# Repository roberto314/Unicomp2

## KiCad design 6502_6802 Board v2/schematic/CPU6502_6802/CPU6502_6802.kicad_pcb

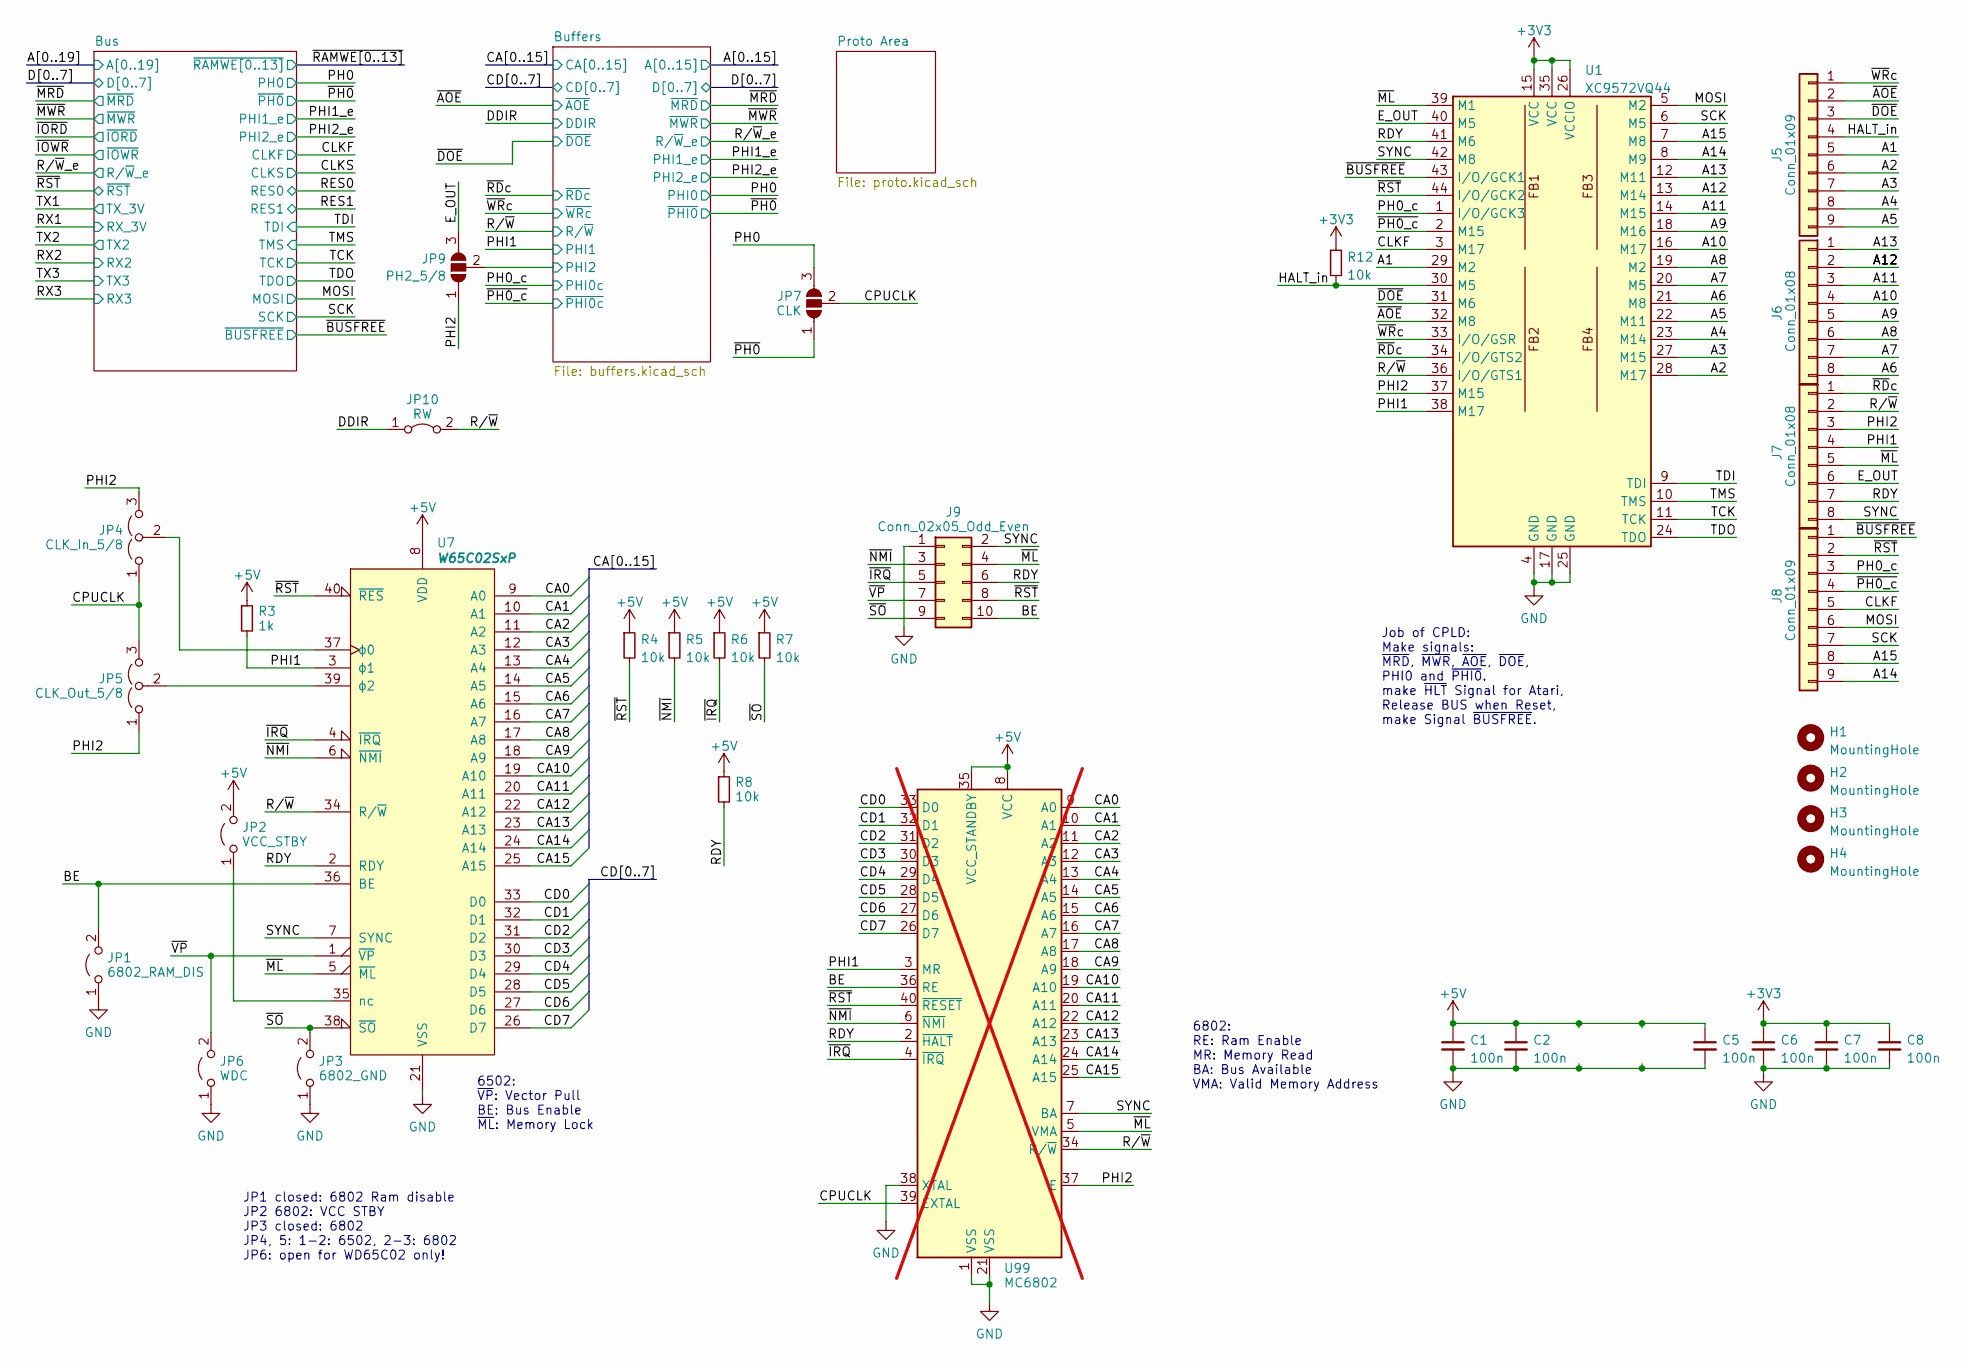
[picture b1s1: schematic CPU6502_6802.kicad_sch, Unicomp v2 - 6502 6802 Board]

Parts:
C1, C2, C5, C6, C7, C8: 100n; C_1206_3216Metric
H1, H2, H3, H4: MountingHole; MountingHole_3.2mm_M3
J5, J8: Conn_01x09; PinHeader_1x09_P2.54mm_Vertical
J6, J7: Conn_01x08; PinHeader_1x08_P2.54mm_Vertical
J9: Conn_02x05_Odd_Even; PinHeader_2x05_P2.54mm_Horizontal
JP1: 6802_RAM_DIS; SolderJumper-2_P1.3mm_Open_RoundedPad1.0x1.5mm
JP2: VCC_STBY; SolderJumper-2_P1.3mm_Open_RoundedPad1.0x1.5mm
JP3: 6802_GND; SolderJumper-2_P1.3mm_Open_RoundedPad1.0x1.5mm
JP4: CLK_In_5/8; SolderJumper-3_P1.3mm_Open_Pad1.0x1.5mm_NumberLabels
JP5: CLK_Out_5/8; SolderJumper-3_P1.3mm_Open_Pad1.0x1.5mm_NumberLabels
JP6: WDC; SolderJumper-2_P1.3mm_Open_RoundedPad1.0x1.5mm
JP7: CLK; SolderJumper-3_P1.3mm_Open_RoundedPad1.0x1.5mm_NumberLabels
JP9: PH2_5/8; SolderJumper-3_P1.3mm_Open_RoundedPad1.0x1.5mm_NumberLabels
JP10: RW; SolderJumper-2_P1.3mm_Bridged_RoundedPad1.0x1.5mm
R3: 1k; R_1206_3216Metric_Pad1.30x1.75mm_HandSolder
R4, R5, R6, R7, R8, R12: 10k; R_1206_3216Metric_Pad1.30x1.75mm_HandSolder
U1: XC9572VQ44; TQFP-44_10x10mm_P0.8mm
U7: W65C02SxP; DIP-40_W15.24mm_Socket_LongPads
U99: MC6802; DIP-40_W15.24mm; not fitted

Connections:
+3V3: C6.1, C7.1, C8.1, R12.1, U1.15 (VCC), U1.26 (VCCIO), U1.35 (VCC); also elsewhere on the board
+5V: C1.1, C2.1, C5.1, JP2.2 (B), R3.1, R4.1, R5.1, R6.1, R7.1, R8.1, U7.8 (VDD), U99.8 (VCC), U99.35 (VCC_STANDBY); also elsewhere on the board
/A1: J5.5, U1.29 (M2); also elsewhere on the board
/A2: J5.6, U1.28 (M17); also elsewhere on the board
/A3: J5.7, U1.27 (M15); also elsewhere on the board
/A4: J5.8, U1.23 (M14); also elsewhere on the board
/A5: J5.9, U1.22 (M11); also elsewhere on the board
/A6: J6.8, U1.21 (M8); also elsewhere on the board
/A7: J6.7, U1.20 (M5); also elsewhere on the board
/A8: J6.6, U1.19 (M2); also elsewhere on the board
/A9: J6.5, U1.18 (M16); also elsewhere on the board
/A10: J6.4, U1.16 (M17); also elsewhere on the board
/A11: J6.3, U1.14 (M15); also elsewhere on the board
/A12: J6.2, U1.13 (M14); also elsewhere on the board
/A13: J6.1, U1.12 (M11); also elsewhere on the board
/A14: J8.9, U1.8 (M9); also elsewhere on the board
/A15: J8.8, U1.7 (M8); also elsewhere on the board
/BE: J9.10, JP1.2 (B), U7.36 (BE), U99.36 (RE)
/Buffers/PHI2: JP9.2 (C); also elsewhere on the board
/CA0: U7.9 (A0), U99.9 (A0); also elsewhere on the board
/CA1: U7.10 (A1), U99.10 (A1); also elsewhere on the board
/CA2: U7.11 (A2), U99.11 (A2); also elsewhere on the board
/CA3: U7.12 (A3), U99.12 (A3); also elsewhere on the board
/CA4: U7.13 (A4), U99.13 (A4); also elsewhere on the board
/CA5: U7.14 (A5), U99.14 (A5); also elsewhere on the board
/CA6: U7.15 (A6), U99.15 (A6); also elsewhere on the board
/CA7: U7.16 (A7), U99.16 (A7); also elsewhere on the board
/CA8: U7.17 (A8), U99.17 (A8); also elsewhere on the board
/CA9: U7.18 (A9), U99.18 (A9); also elsewhere on the board
/CA10: U7.19 (A10), U99.19 (A10); also elsewhere on the board
/CA11: U7.20 (A11), U99.20 (A11); also elsewhere on the board
/CA12: U7.22 (A12), U99.22 (A12); also elsewhere on the board
/CA13: U7.23 (A13), U99.23 (A13); also elsewhere on the board
/CA14: U7.24 (A14), U99.24 (A14); also elsewhere on the board
/CA15: U7.25 (A15), U99.25 (A15); also elsewhere on the board
/CD0: U7.33 (D0), U99.33 (D0); also elsewhere on the board
/CD1: U7.32 (D1), U99.32 (D1); also elsewhere on the board
/CD2: U7.31 (D2), U99.31 (D2); also elsewhere on the board
/CD3: U7.30 (D3), U99.30 (D3); also elsewhere on the board
/CD4: U7.29 (D4), U99.29 (D4); also elsewhere on the board
/CD5: U7.28 (D5), U99.28 (D5); also elsewhere on the board
/CD6: U7.27 (D6), U99.27 (D6); also elsewhere on the board
/CD7: U7.26 (D7), U99.26 (D7); also elsewhere on the board
/CLKF: J8.5, U1.3 (M17); also elsewhere on the board
/CPUCLK: JP4.1 (A), JP5.3 (B), JP7.2 (C), U99.39 (EXTAL)
/DDIR: JP10.1 (A); also elsewhere on the board
/E_OUT: J7.6, JP9.3 (B), U1.40 (M5)
/HALT_in: J5.4, R12.2, U1.30 (M5)
/MOSI: J8.6, U1.5 (M2); also elsewhere on the board
/PH0: JP7.3 (B); also elsewhere on the board
/PH0_c: J8.3, U1.1 (I/O/GCK3); also elsewhere on the board
/PHI1: J7.4, R3.2, U1.38 (M17), U7.3 (ϕ1), U99.3 (MR); also elsewhere on the board
/PHI2: J7.3, JP4.3 (B), JP5.1 (A), JP9.1 (A), U1.37 (M15), U99.37 (E)
/RDY: J7.7, J9.6, R8.2, U1.41 (M6), U7.2 (RDY), U99.2 (~HALT)
/R/~W: J7.2, JP10.2 (B), U1.36 (I/O/GTS1), U7.34 (R/~W), U99.34 (R/~W); also elsewhere on the board
/SCK: J8.7, U1.6 (M5); also elsewhere on the board
/SYNC: J7.8, J9.2, U1.42 (M8), U7.7 (SYNC), U99.7 (BA)
/TCK: U1.11 (TCK); also elsewhere on the board
/TDI: U1.9 (TDI); also elsewhere on the board
/TDO: U1.24 (TDO); also elsewhere on the board
/TMS: U1.10 (TMS); also elsewhere on the board
/~AOE: J5.2, U1.32 (M8); also elsewhere on the board
/~BUSFREE: J8.1, U1.43 (I/O/GCK1); also elsewhere on the board
/~DOE: J5.3, U1.31 (M6); also elsewhere on the board
/~IRQ: J9.5, R6.2, U7.4 (~IRQ), U99.4 (~IRQ)
/~ML: J7.5, J9.4, U1.39 (M1), U7.5 (~ML), U99.5 (VMA)
/~NMI: J9.3, R5.2, U7.6 (~NMI), U99.6 (~NMI)
/~PH0_c: J8.4, U1.2 (M15); also elsewhere on the board
/~PH0: JP7.1 (A); also elsewhere on the board
/~RDc: J7.1, U1.34 (I/O/GTS2); also elsewhere on the board
/~RST: J8.2, J9.8, R4.2, U1.44 (I/O/GCK2), U7.40 (~RES), U99.40 (~RESET); also elsewhere on the board
/~SO: J9.9, JP3.2 (B), R7.2, U7.38 (~SO)
/~VP: J9.7, JP6.2 (B), U7.1 (~VP)
/~WRc: J5.1, U1.33 (I/O/GSR); also elsewhere on the board
GND: C1.2, C2.2, C5.2, C6.2, C7.2, C8.2, J9.1, JP1.1 (A), JP3.1 (A), JP6.1 (A), U1.4 (GND), U1.17 (GND), U1.25 (GND), U7.21 (VSS), U99.1 (VSS), U99.21 (VSS), U99.38 (XTAL); also elsewhere on the board
unnamed: JP2.1 (A), U7.35 (nc)
unnamed: JP4.2 (C), U7.37 (ϕ0)
unnamed: JP5.2 (C), U7.39 (ϕ2)

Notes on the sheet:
JP1 closed: 6802 Ram disable JP2 6802: VCC STBY JP3 closed: 6802 JP4, 5: 1-2: 6502, 2-3: 6802 JP6: open for WD65C02 only!
6802: RE: Ram Enable MR: Memory Read BA: Bus Available VMA: Valid Memory Address
Job of CPLD: Make signals: ~{MRD}, ~{MWR}, ~{AOE}, ~{DOE}, PHI0 and ~{PHI0}. make ~{HLT} Signal for Atari, Release BUS when Reset, make Signal ~{BUSFREE}.
6502: ~{VP}: Vector Pull BE: Bus Enable ~{ML}: Memory Lock

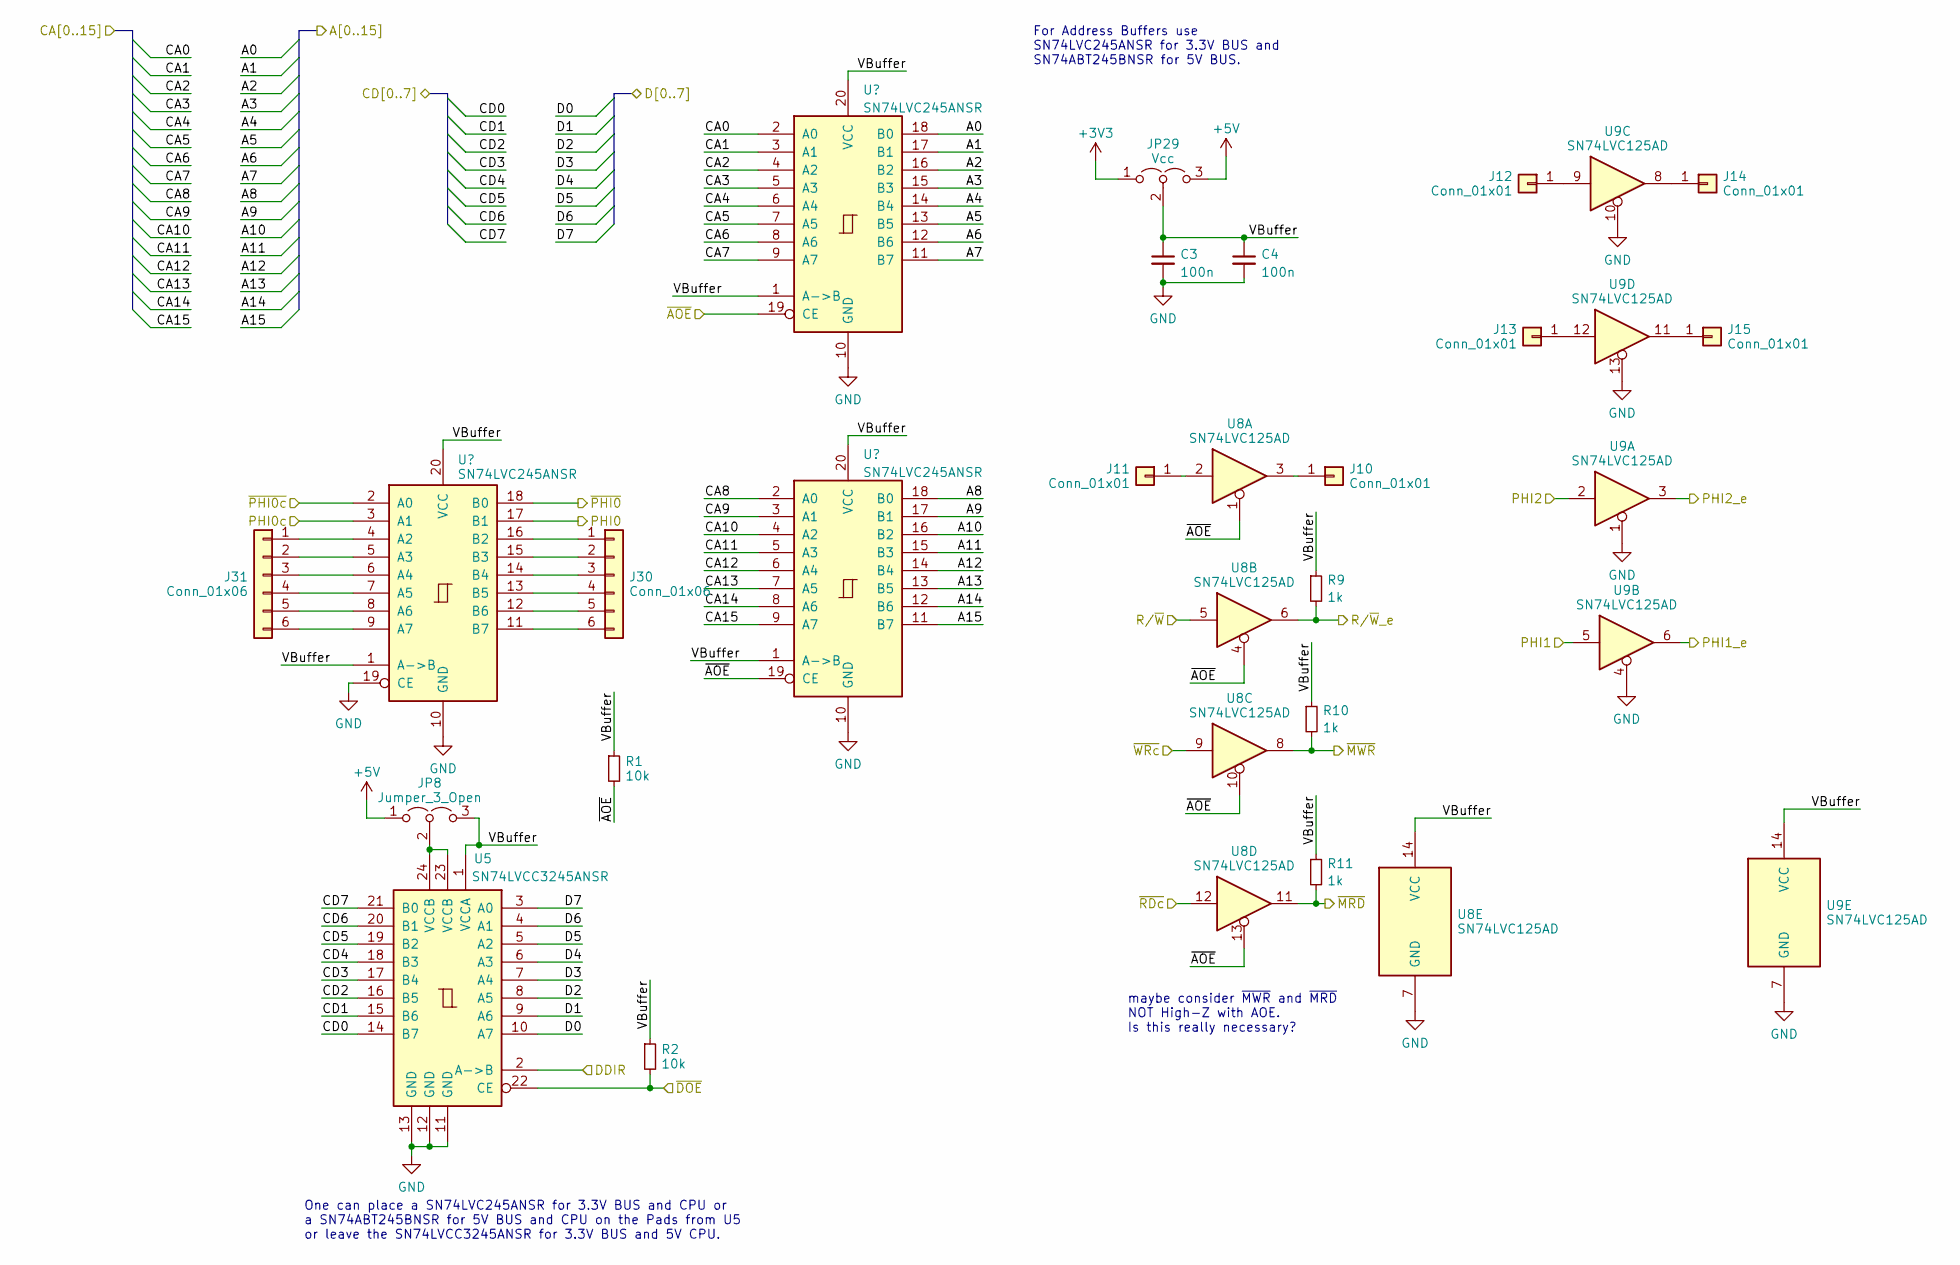
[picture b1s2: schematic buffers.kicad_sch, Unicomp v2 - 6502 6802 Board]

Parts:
C3, C4: 100n; C_1206_3216Metric
J10, J11, J12, J13, J14, J15: Conn_01x01; PinHeader_1x01_P1.27mm_Vertical
J30, J31: Conn_01x06; PinHeader_1x06_P1.27mm_Vertical
JP8: Jumper_3_Open; SolderJumper-3_P1.3mm_Open_Pad1.0x1.5mm_NumberLabels
JP29: Vcc; SolderJumper-3_P1.3mm_Open_RoundedPad1.0x1.5mm_NumberLabels
R1, R2: 10k; R_1206_3216Metric_Pad1.30x1.75mm_HandSolder
R9, R10, R11: 1k; R_1206_3216Metric_Pad1.30x1.75mm_HandSolder
U2, U3, U6: SN74LVC245ANSR; SO-20_5.3x12.6mm_P1.27mm
U5: SN74LVCC3245ANSR; SO-24_5.3x15mm_P1.27mm
U8, U9: SN74LVC125AD; SOIC-14_3.9x8.7mm_P1.27mm

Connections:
+3V3: JP29.1 (A); also elsewhere on the board
+5V: JP8.1 (A), JP29.3 (B); also elsewhere on the board
/A0: U2.18 (B0); also elsewhere on the board
/A1: U2.17 (B1); also elsewhere on the board
/A2: U2.16 (B2); also elsewhere on the board
/A3: U2.15 (B3); also elsewhere on the board
/A4: U2.14 (B4); also elsewhere on the board
/A5: U2.13 (B5); also elsewhere on the board
/A6: U2.12 (B6); also elsewhere on the board
/A7: U2.11 (B7); also elsewhere on the board
/A8: U3.18 (B0); also elsewhere on the board
/A9: U3.17 (B1); also elsewhere on the board
/A10: U3.16 (B2); also elsewhere on the board
/A11: U3.15 (B3); also elsewhere on the board
/A12: U3.14 (B4); also elsewhere on the board
/A13: U3.13 (B5); also elsewhere on the board
/A14: U3.12 (B6); also elsewhere on the board
/A15: U3.11 (B7); also elsewhere on the board
/Buffers/PHI2: U9.2; also elsewhere on the board
/Buffers/VBuffer: C3.1, C4.1, JP8.3 (B), JP29.2 (C), R1.1, R2.1, R9.1, R10.1, R11.1, U2.1 (A->B), U2.20 (VCC), U3.1 (A->B), U3.20 (VCC), U5.1 (VCCA), U6.1 (A->B), U6.20 (VCC), U8.14 (VCC), U9.14 (VCC)
/CA0: U2.2 (A0); also elsewhere on the board
/CA1: U2.3 (A1); also elsewhere on the board
/CA2: U2.4 (A2); also elsewhere on the board
/CA3: U2.5 (A3); also elsewhere on the board
/CA4: U2.6 (A4); also elsewhere on the board
/CA5: U2.7 (A5); also elsewhere on the board
/CA6: U2.8 (A6); also elsewhere on the board
/CA7: U2.9 (A7); also elsewhere on the board
/CA8: U3.2 (A0); also elsewhere on the board
/CA9: U3.3 (A1); also elsewhere on the board
/CA10: U3.4 (A2); also elsewhere on the board
/CA11: U3.5 (A3); also elsewhere on the board
/CA12: U3.6 (A4); also elsewhere on the board
/CA13: U3.7 (A5); also elsewhere on the board
/CA14: U3.8 (A6); also elsewhere on the board
/CA15: U3.9 (A7); also elsewhere on the board
/CD0: U5.14 (B7); also elsewhere on the board
/CD1: U5.15 (B6); also elsewhere on the board
/CD2: U5.16 (B5); also elsewhere on the board
/CD3: U5.17 (B4); also elsewhere on the board
/CD4: U5.18 (B3); also elsewhere on the board
/CD5: U5.19 (B2); also elsewhere on the board
/CD6: U5.20 (B1); also elsewhere on the board
/CD7: U5.21 (B0); also elsewhere on the board
/D0: U5.10 (A7); also elsewhere on the board
/D1: U5.9 (A6); also elsewhere on the board
/D2: U5.8 (A5); also elsewhere on the board
/D3: U5.7 (A4); also elsewhere on the board
/D4: U5.6 (A3); also elsewhere on the board
/D5: U5.5 (A2); also elsewhere on the board
/D6: U5.4 (A1); also elsewhere on the board
/D7: U5.3 (A0); also elsewhere on the board
/DDIR: U5.2 (A->B); also elsewhere on the board
/PH0: U6.17 (B1); also elsewhere on the board
/PH0_c: U6.3 (A1); also elsewhere on the board
/PHI1: U9.5; also elsewhere on the board
/PHI1_e: U9.6; also elsewhere on the board
/PHI2_e: U9.3; also elsewhere on the board
/R/~W: U8.5; also elsewhere on the board
/R/~W_e: R9.2, U8.6; also elsewhere on the board
/~AOE: R1.2, U2.19 (CE), U3.19 (CE), U8.1, U8.4, U8.10, U8.13; also elsewhere on the board
/~DOE: R2.2, U5.22 (CE); also elsewhere on the board
/~MRD: R11.2, U8.11; also elsewhere on the board
/~MWR: R10.2, U8.8; also elsewhere on the board
/~PH0_c: U6.2 (A0); also elsewhere on the board
/~PH0: U6.18 (B0); also elsewhere on the board
/~RDc: U8.12; also elsewhere on the board
/~WRc: U8.9; also elsewhere on the board
GND: C3.2, C4.2, U2.10 (GND), U3.10 (GND), U5.11 (GND), U5.12 (GND), U5.13 (GND), U6.10 (GND), U6.19 (CE), U8.7 (GND), U9.1, U9.4, U9.7 (GND), U9.10, U9.13; also elsewhere on the board
unnamed: J10.1, U8.3
unnamed: J11.1, U8.2
unnamed: J12.1, U9.9
unnamed: J13.1, U9.12
unnamed: J14.1, U9.8
unnamed: J15.1, U9.11
unnamed: J30.1, U6.16 (B2)
unnamed: J30.2, U6.15 (B3)
unnamed: J30.3, U6.14 (B4)
unnamed: J30.4, U6.13 (B5)
unnamed: J30.5, U6.12 (B6)
unnamed: J30.6, U6.11 (B7)
unnamed: J31.1, U6.4 (A2)
unnamed: J31.2, U6.5 (A3)
unnamed: J31.3, U6.6 (A4)
unnamed: J31.4, U6.7 (A5)
unnamed: J31.5, U6.8 (A6)
unnamed: J31.6, U6.9 (A7)
unnamed: JP8.2 (C), U5.23 (VCCB), U5.24 (VCCB)

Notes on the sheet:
maybe consider ~{MWR} and ~{MRD} NOT High-Z with AOE. Is this really necessary?
One can place a SN74LVC245ANSR for 3.3V BUS and CPU or a SN74ABT245BNSR for 5V BUS and CPU on the Pads from U5 or leave the SN74LVCC3245ANSR for 3.3V BUS and 5V CPU.
For Address Buffers use SN74LVC245ANSR for 3.3V BUS and SN74ABT245BNSR for 5V BUS.

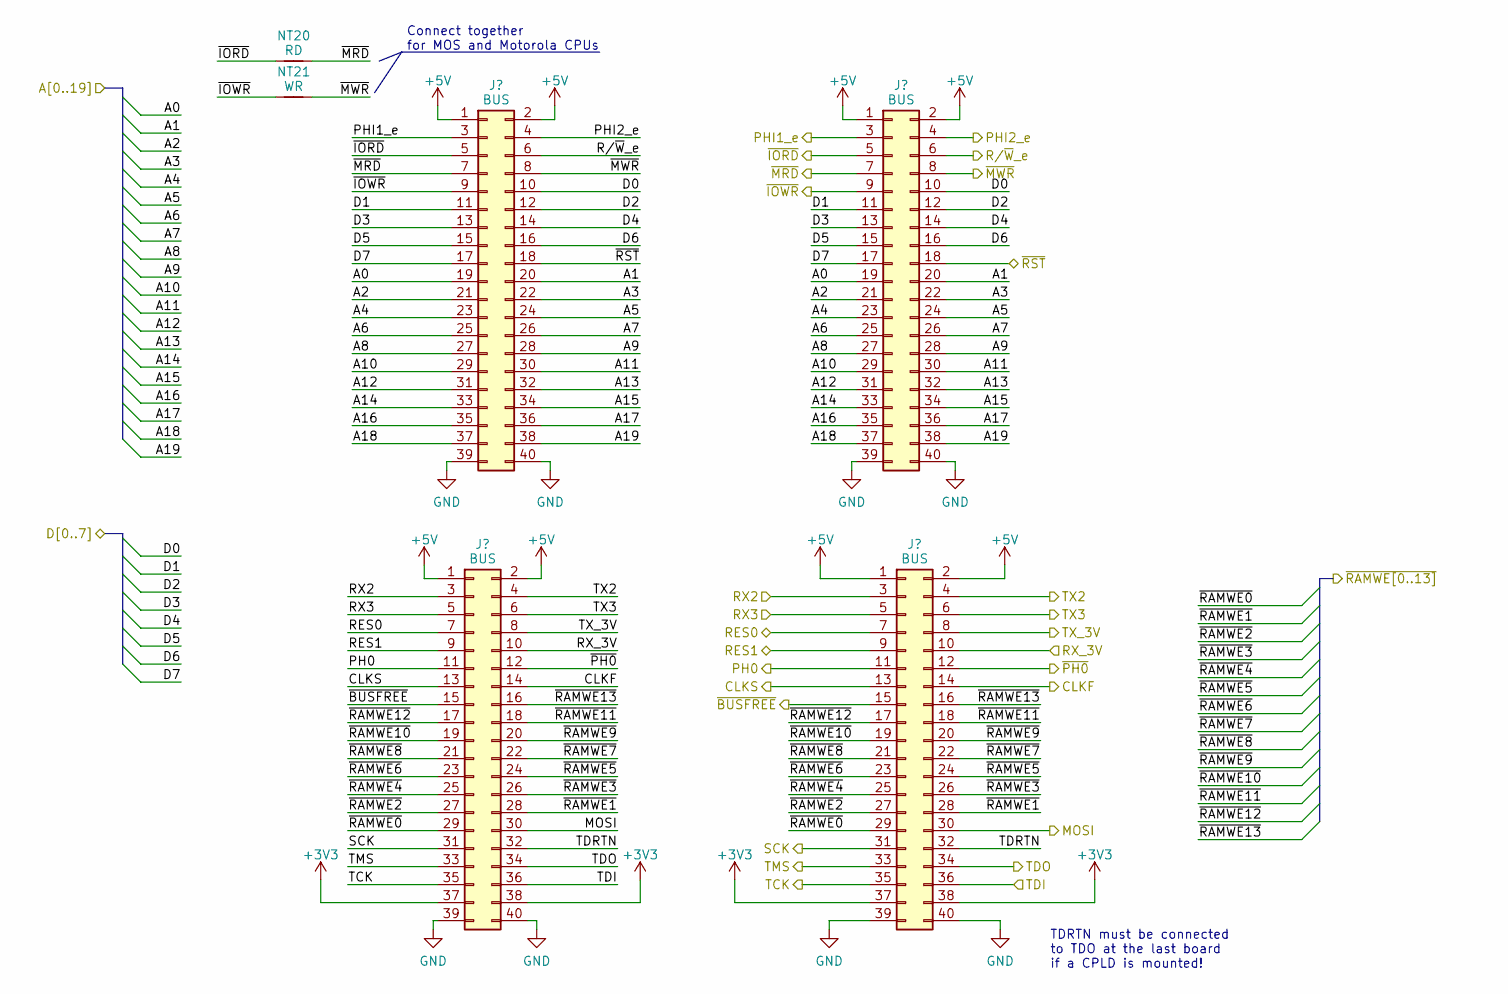
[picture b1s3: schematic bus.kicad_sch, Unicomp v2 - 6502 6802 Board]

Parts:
J1, J2, J3, J4: BUS; PinSocket_2x20_P2.54mm_Vertical
NT20: RD; NetTie-2_SMD_Pad0.5mm
NT21: WR; NetTie-2_SMD_Pad0.5mm

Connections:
+3V3: J2.37, J2.38, J4.37, J4.38; also elsewhere on the board
+5V: J1.1, J1.2, J2.1, J2.2, J3.1, J3.2, J4.1, J4.2; also elsewhere on the board
/A0: J1.19, J3.19; also elsewhere on the board
/A1: J1.20, J3.20; also elsewhere on the board
/A2: J1.21, J3.21; also elsewhere on the board
/A3: J1.22, J3.22; also elsewhere on the board
/A4: J1.23, J3.23; also elsewhere on the board
/A5: J1.24, J3.24; also elsewhere on the board
/A6: J1.25, J3.25; also elsewhere on the board
/A7: J1.26, J3.26; also elsewhere on the board
/A8: J1.27, J3.27; also elsewhere on the board
/A9: J1.28, J3.28; also elsewhere on the board
/A10: J1.29, J3.29; also elsewhere on the board
/A11: J1.30, J3.30; also elsewhere on the board
/A12: J1.31, J3.31; also elsewhere on the board
/A13: J1.32, J3.32; also elsewhere on the board
/A14: J1.33, J3.33; also elsewhere on the board
/A15: J1.34, J3.34; also elsewhere on the board
/A16: J1.35, J3.35
/A17: J1.36, J3.36
/A18: J1.37, J3.37
/A19: J1.38, J3.38
/Bus/TDRTN: J2.32, J4.32
/CLKF: J2.14, J4.14; also elsewhere on the board
/CLKS: J2.13, J4.13
/D0: J1.10, J3.10; also elsewhere on the board
/D1: J1.11, J3.11; also elsewhere on the board
/D2: J1.12, J3.12; also elsewhere on the board
/D3: J1.13, J3.13; also elsewhere on the board
/D4: J1.14, J3.14; also elsewhere on the board
/D5: J1.15, J3.15; also elsewhere on the board
/D6: J1.16, J3.16; also elsewhere on the board
/D7: J1.17, J3.17; also elsewhere on the board
/MOSI: J2.30, J4.30; also elsewhere on the board
/PH0: J2.11, J4.11; also elsewhere on the board
/PHI1_e: J1.3, J3.3; also elsewhere on the board
/PHI2_e: J1.4, J3.4; also elsewhere on the board
/RES0: J2.7, J4.7
/RES1: J2.9, J4.9
/RX1: J2.10, J4.10
/RX2: J2.3, J4.3
/RX3: J2.5, J4.5
/R/~W_e: J1.6, J3.6; also elsewhere on the board
/SCK: J2.31, J4.31; also elsewhere on the board
/TCK: J2.35, J4.35; also elsewhere on the board
/TDI: J2.36, J4.36; also elsewhere on the board
/TDO: J2.34, J4.34; also elsewhere on the board
/TMS: J2.33, J4.33; also elsewhere on the board
/TX1: J2.8, J4.8
/TX2: J2.4, J4.4
/TX3: J2.6, J4.6
/~BUSFREE: J2.15, J4.15; also elsewhere on the board
/~IORD: J1.5, J3.5, NT20.1
/~IOWR: J1.9, J3.9, NT21.1
/~MRD: J1.7, J3.7, NT20.2; also elsewhere on the board
/~MWR: J1.8, J3.8, NT21.2; also elsewhere on the board
/~PH0: J2.12, J4.12; also elsewhere on the board
/~RAMWE0: J2.29, J4.29
/~RAMWE1: J2.28, J4.28
/~RAMWE2: J2.27, J4.27
/~RAMWE3: J2.26, J4.26
/~RAMWE4: J2.25, J4.25
/~RAMWE5: J2.24, J4.24
/~RAMWE6: J2.23, J4.23
/~RAMWE7: J2.22, J4.22
/~RAMWE8: J2.21, J4.21
/~RAMWE9: J2.20, J4.20
/~RAMWE10: J2.19, J4.19
/~RAMWE11: J2.18, J4.18
/~RAMWE12: J2.17, J4.17
/~RAMWE13: J2.16, J4.16
/~RST: J1.18, J3.18; also elsewhere on the board
GND: J1.39, J1.40, J2.39, J2.40, J3.39, J3.40, J4.39, J4.40; also elsewhere on the board

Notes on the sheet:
Connect together for MOS and Motorola CPUs
TDRTN must be connected to TDO at the last board if a CPLD is mounted!

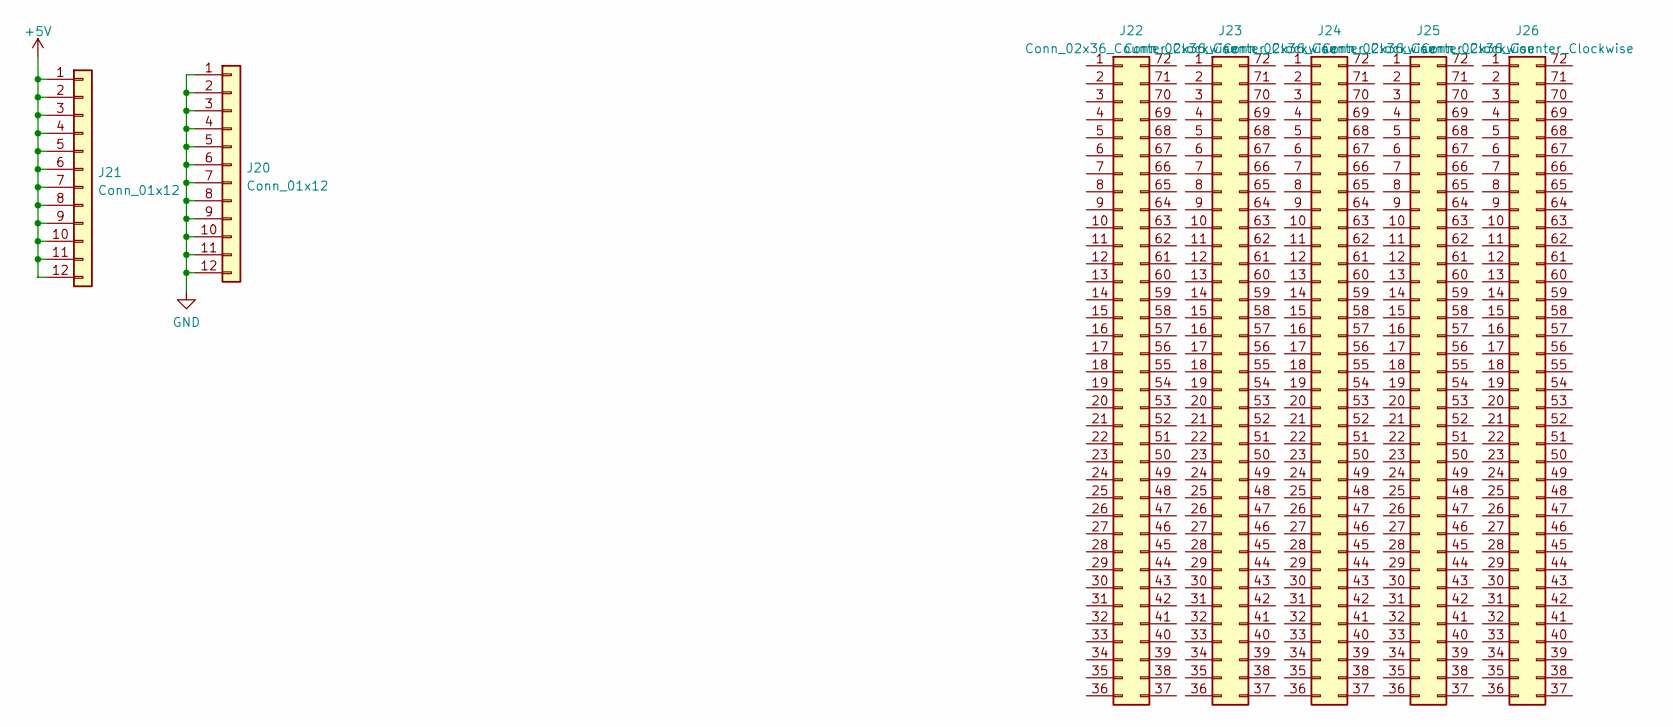
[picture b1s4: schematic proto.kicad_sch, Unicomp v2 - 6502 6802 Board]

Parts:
J20, J21: Conn_01x12; PinHeader_1x12_P2.54mm_Vertical
J22, J23, J24, J25, J26: Conn_02x36_Counter_Clockwise; Proto_2x36

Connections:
+5V: J21.1, J21.2, J21.3, J21.4, J21.5, J21.6, J21.7, J21.8, J21.9, J21.10, J21.11, J21.12; also elsewhere on the board
GND: J20.1, J20.2, J20.3, J20.4, J20.5, J20.6, J20.7, J20.8, J20.9, J20.10, J20.11, J20.12; also elsewhere on the board

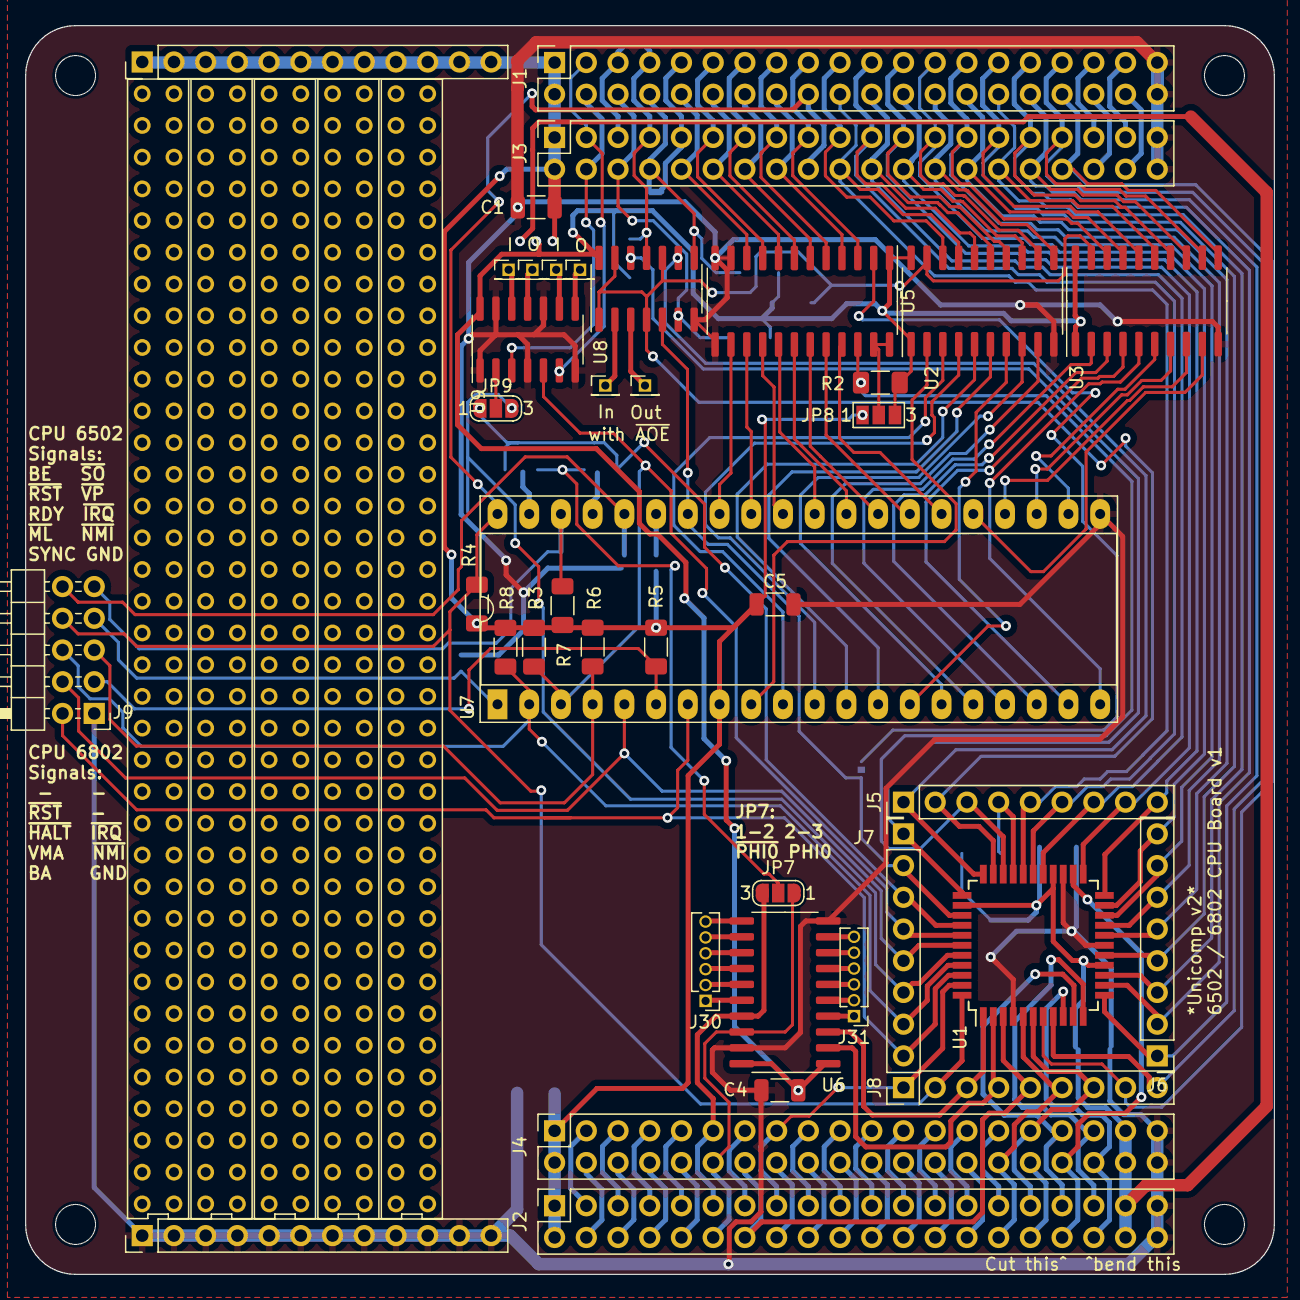
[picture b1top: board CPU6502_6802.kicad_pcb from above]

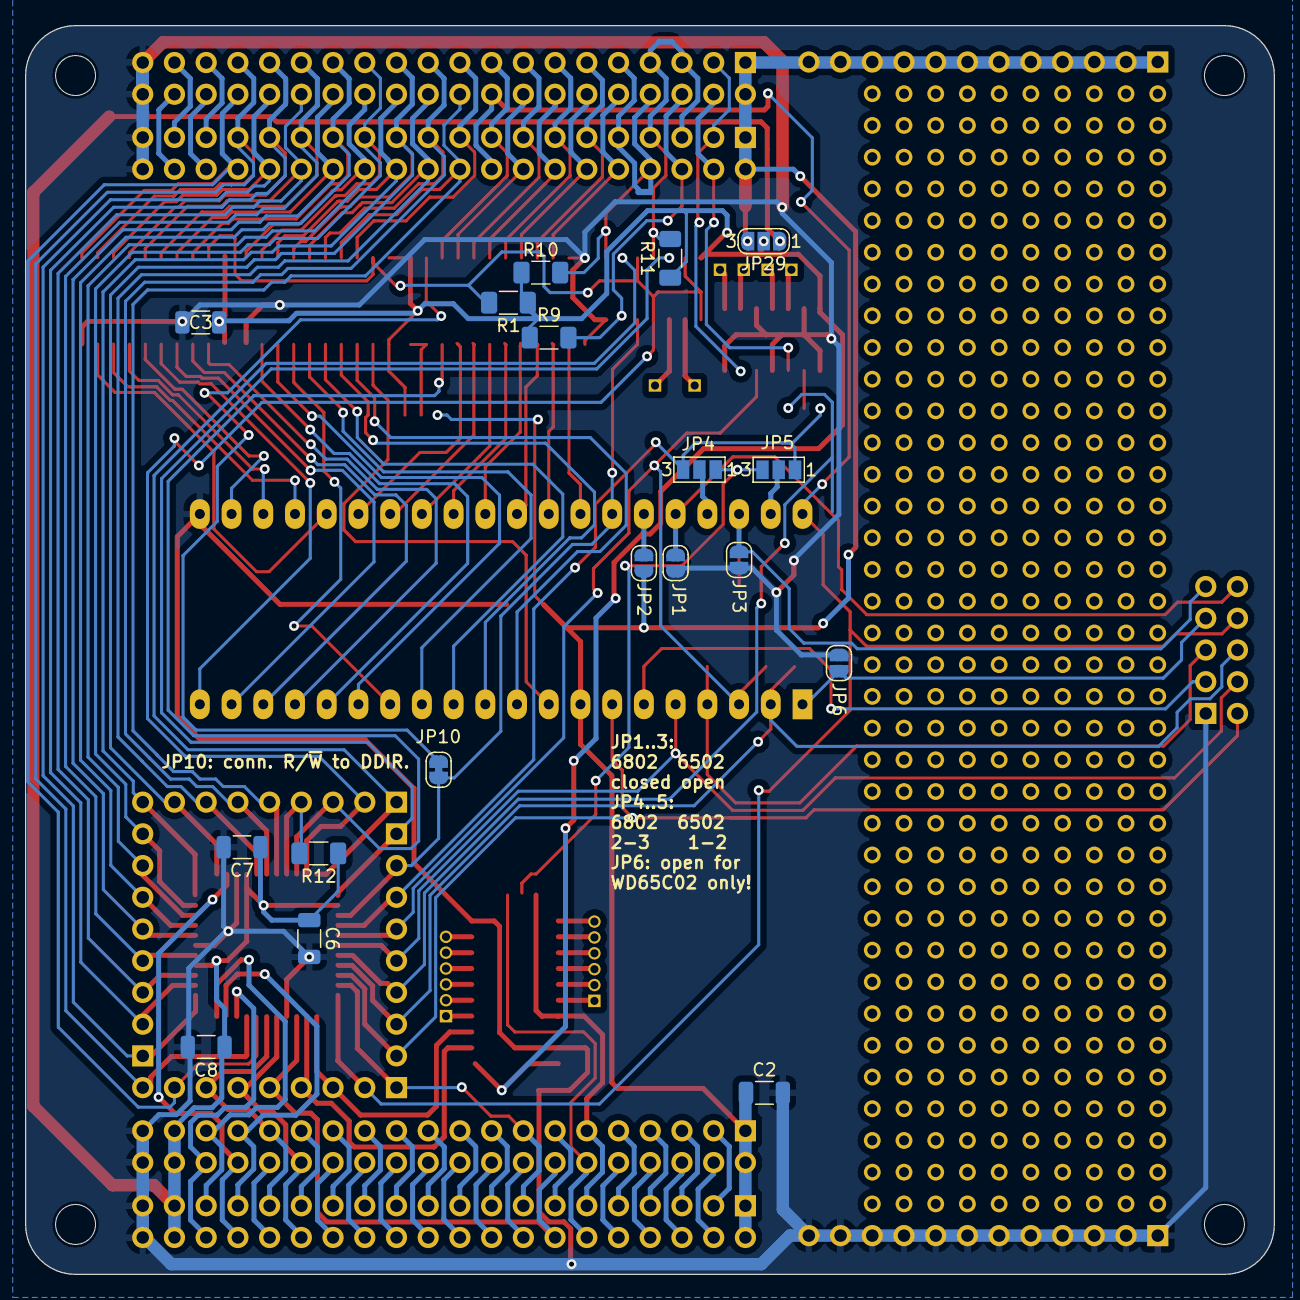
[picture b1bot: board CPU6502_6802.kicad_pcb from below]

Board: 2 copper layers, 100.0 x 100.0 mm, 69 parts (20 on the bottom side), 142 nets.
